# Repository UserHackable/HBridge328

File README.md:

## HBridge328 

### Board dimensions

* (200000, 130000) original units
* (2.0000, 1.3000) inches
* (50.8000, 33.0200) mm

[gerbers](%*_gerber.zip)

| Front | Back |
| --- | --- |
|  |  |

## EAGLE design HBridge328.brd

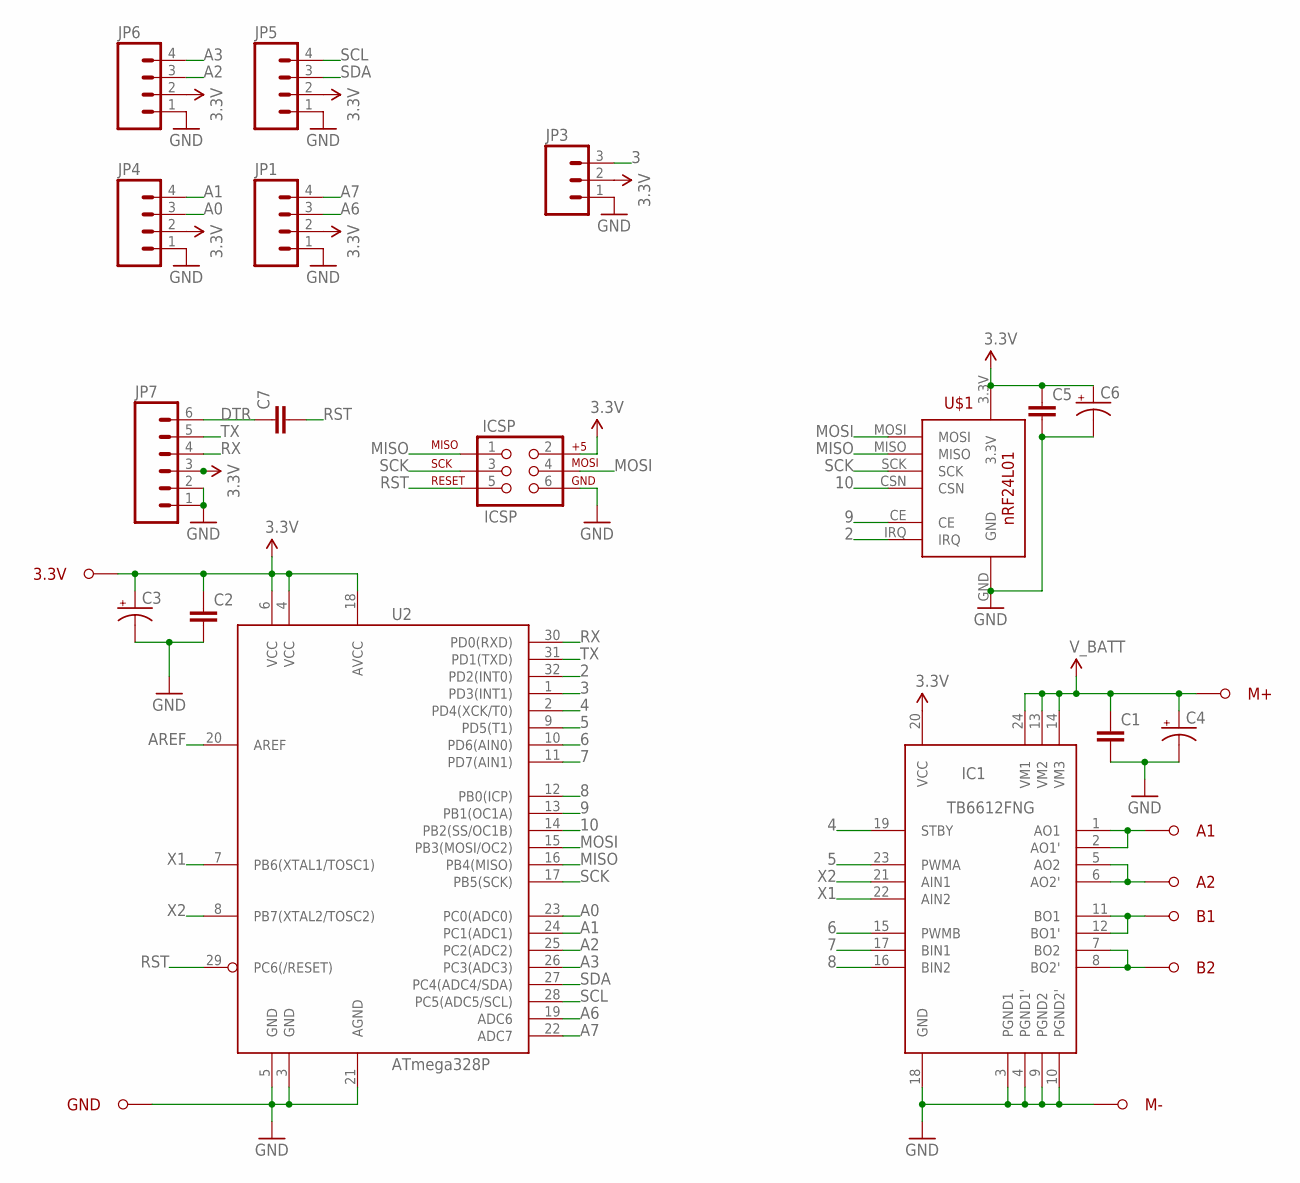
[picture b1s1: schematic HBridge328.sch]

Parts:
3.3V: M1; M1_NO_STRAIN
A1, A2: M1; M1_NO_STRAIN
B1, B2: M1; M1_NO_STRAIN
C1, C2, C5, C7: CAP1206; 1206
C3, C4, C6: CAP_POL1206; EIA3216
GND: M1; M1_NO_STRAIN
IC1: TB6612; SSOP24
ICSP: ICSP; 2X3-NS
JP1, JP4, JP5, JP6: M04PTH; 1X04
JP3: M03PTH; 1X03
JP7: M06SILK_FEMALE_PTH; 1X06
M+: M1; M1_NO_STRAIN
M-: M1; M1_NO_STRAIN
U2: ATmega328P; TQFP32-08
U$1: RF24_MODULE; RF24_SOCKET

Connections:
2: U2.32 (PD2(INT0)), U$1.IRQ
3: JP3.3, U2.1 (PD3(INT1))
3.3V: 3.3V.P$1, C2.1, C3.A (+), C5.1, C6.A (+), IC1.20 (VCC), ICSP.2 (V+), JP1.2, JP3.2, JP4.2, JP5.2, JP6.2, JP7.3, U2.4 (VCC), U2.6 (VCC), U2.18 (AVCC), U$1.3.3V
4: IC1.19 (STBY), U2.2 (PD4(XCK/T0))
5: IC1.23 (PWMA), U2.9 (PD5(T1))
6: IC1.15 (PWMB), U2.10 (PD6(AIN0))
7: IC1.17 (BIN1), U2.11 (PD7(AIN1))
8: IC1.16 (BIN2), U2.12 (PB0(ICP))
9: U2.13 (PB1(OC1A)), U$1.CE
10: U2.14 (PB2(SS/OC1B)), U$1.CSN
A0: JP4.3, U2.23 (PC0(ADC0))
A1: JP4.4, U2.24 (PC1(ADC1))
A2: JP6.3, U2.25 (PC2(ADC2))
A3: JP6.4, U2.26 (PC3(ADC3))
A6: JP1.3, U2.19 (ADC6)
A7: JP1.4, U2.22 (ADC7)
AREF: U2.20 (AREF)
DTR: C7.1, JP7.6
GND: C1.2, C2.2, C3.C (-), C4.C (-), C5.2, C6.C (-), GND.P$1, IC1.3 (PGND1), IC1.4 (PGND1'), IC1.9 (PGND2), IC1.10 (PGND2'), IC1.18 (GND), ICSP.6 (GND), JP1.1, JP3.1, JP4.1, JP5.1, JP6.1, JP7.1, JP7.2, M-.P$1, U2.3 (GND), U2.5 (GND), U2.21 (AGND), U$1.GND
MISO: ICSP.1 (MISO), U2.16 (PB4(MISO)), U$1.MISO
MOSI: ICSP.4 (MOSI), U2.15 (PB3(MOSI/OC2)), U$1.MOSI
unnamed: A1.P$1, IC1.1 (AO1), IC1.2 (AO1')
unnamed: A2.P$1, IC1.5 (AO2), IC1.6 (AO2')
unnamed: B1.P$1, IC1.11 (BO1), IC1.12 (BO1')
unnamed: B2.P$1, IC1.7 (BO2), IC1.8 (BO2')
RST: C7.2, ICSP.5 (RST), U2.29 (PC6(/RESET))
RX: JP7.4, U2.30 (PD0(RXD))
SCK: ICSP.3 (SCK), U2.17 (PB5(SCK)), U$1.SCK
SCL: JP5.4, U2.28 (PC5(ADC5/SCL))
SDA: JP5.3, U2.27 (PC4(ADC4/SDA))
TX: JP7.5, U2.31 (PD1(TXD))
V_BATT: C1.1, C4.A (+), IC1.13 (VM2), IC1.14 (VM3), IC1.24 (VM1), M+.P$1
X1: IC1.22 (AIN2), U2.7 (PB6(XTAL1/TOSC1))
X2: IC1.21 (AIN1), U2.8 (PB7(XTAL2/TOSC2))

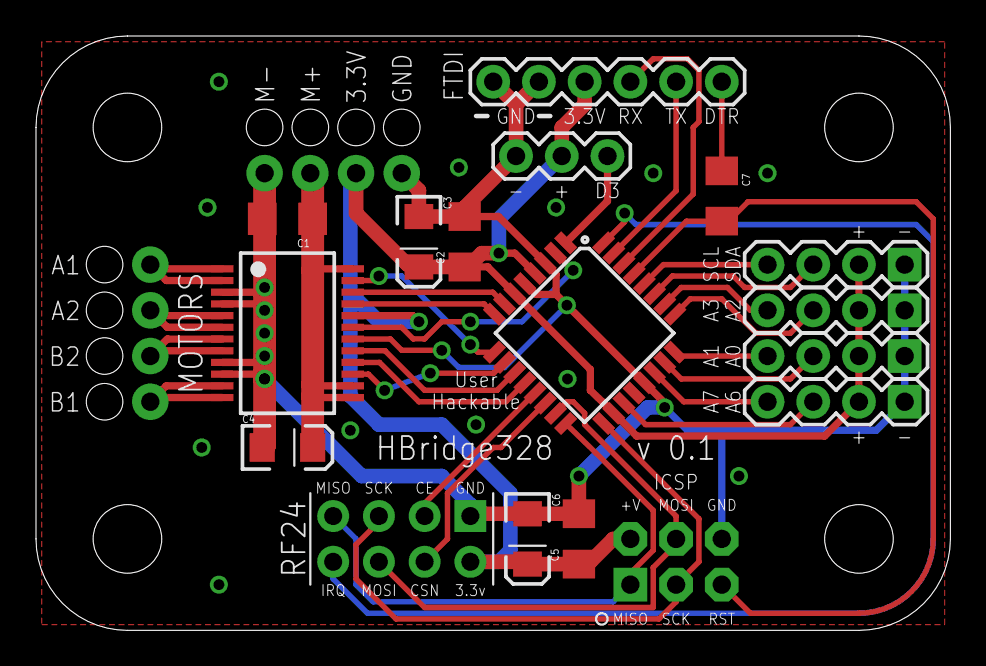
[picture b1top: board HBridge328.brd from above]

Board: 2 copper layers, 50.8 x 33.0 mm, 25 parts (0 on the bottom side), 33 nets.

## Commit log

2016-04-08 from Makefile

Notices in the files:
parts and their libraries:
SparkFun-Connectors: Licensing: Creative Commons ShareAlike 4.0 International - https://creativecommons.org/licenses/by-sa/4.0
